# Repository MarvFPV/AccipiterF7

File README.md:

# Accipiter F7
A flight controller built for Rotorflight firmware and their F7A target. 
For more info go check out my [blog entry](https://mschnabel.com/2025/01/27/AccipiterF7/) on it!

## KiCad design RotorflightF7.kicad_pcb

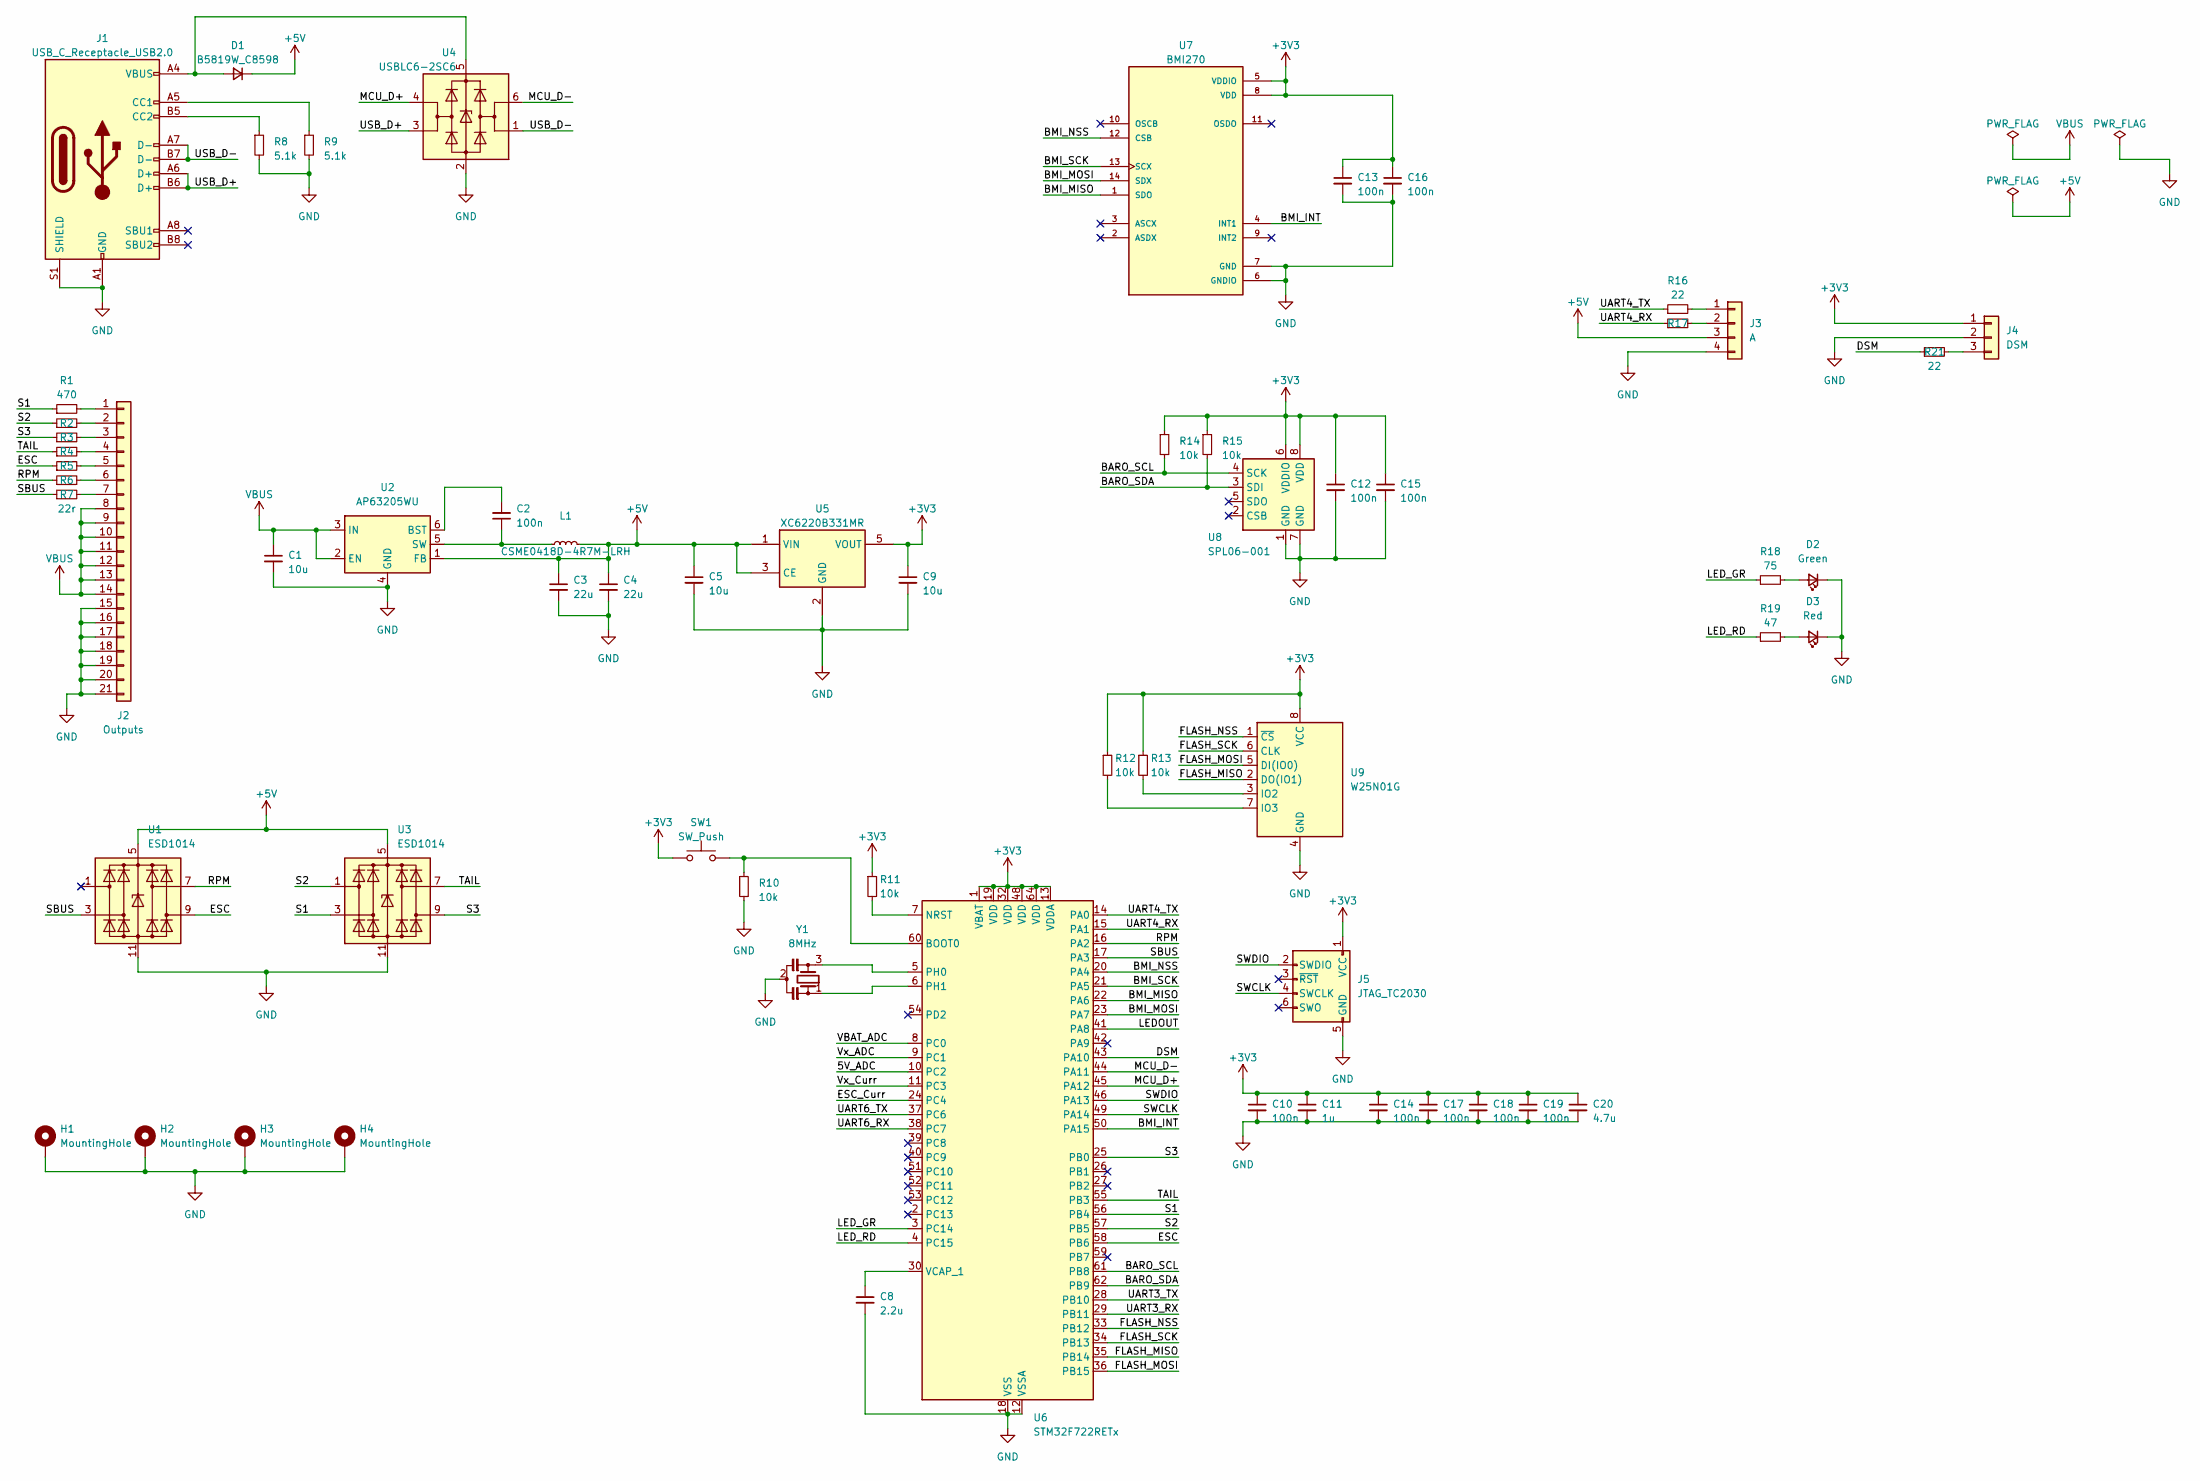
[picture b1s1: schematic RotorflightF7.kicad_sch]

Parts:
C1, C5, C9: 10u; C_0603_1608Metric
C2, C10, C12, C13, C14, C15, C16, C17, C18, C19: 100n; C_0402_1005Metric
C3, C4: 22u; C_0603_1608Metric
C8: 2.2u; C_0402_1005Metric
C11: 1u; C_0402_1005Metric
C20: 4.7u; C_0402_1005Metric
D1: B5819W_C8598; D_SOD-123
D2: Green; LED_0603_1608Metric
D3: Red; LED_0603_1608Metric
H1, H2, H3, H4: MountingHole; MountingHole_2.2mm_M2_Pad_Via
J1: USB_C_Receptacle_USB2.0; USB_C_Receptacle_HRO_TYPE-C-31-M-12
J2: Outputs; 7xServo_Vertical
J3: A; JST_GH_BM04B-GHS-TBT_1x04-1MP_P1.25mm_Vertical
J4: DSM; JST_ZH_B3B-ZR_1x03_P1.50mm_Vertical
J5: JTAG_TC2030; CON_TC2030_outlined
L1: CSME0418D-4R7M-LRH; L_Vishay_IFSC-1515AH_4x4x1.8mm
R1, R2, R3, R4, R5, R6: 470; R_0402_1005Metric
R7: 22r; R_0402_1005Metric
R8, R9: 5.1k; R_0402_1005Metric
R10, R11, R12, R13, R14, R15: 10k; R_0402_1005Metric
R16, R17, R21: 22; R_0402_1005Metric
R18: 75; R_0402_1005Metric
R19: 47; R_0402_1005Metric
SW1: SW_Push; SW_Push_SPST_NO_Alps_SKRK
U1, U3: ESD1014; DFN-10-1EP_2.6x2.6mm_P0.5mm_EP1.3x2.2mm
U2: AP63205WU; TSOT-23-6
U4: USBLC6-2SC6; SOT-23-6
U5: XC6220B331MR; SOT-23-5
U6: STM32F722RETx; LQFP-64_10x10mm_P0.5mm
U7: BMI270; XDCR_BMI270
U8: SPL06-001; Bosch_LGA-8_2x2.5mm_P0.65mm_ClockwisePinNumbering
U9: W25N01G; WSON-8-1EP_8x6mm_P1.27mm_EP3.4x4.3mm
Y1: 8MHz; Resonator_SMD_Murata_CSTxExxV-3Pin_3.0x1.1mm

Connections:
+3V3: C9.1, C10.1, C11.1, C12.1, C13.1, C14.1, C15.1, C16.1, C17.1, C18.1, C19.1, C20.1, J4.1, J5.1 (VCC), R11.1, R12.1, R13.1, R14.1, R15.1, SW1.1, U5.5 (VOUT), U6.1 (VBAT), U6.13 (VDDA), U6.19 (VDD), U6.32 (VDD), U6.48 (VDD), U6.64 (VDD), U7.5 (VDDIO), U7.8 (VDD), U8.6 (VDDIO), U8.8 (VDD), U9.8 (VCC)
+5V: C3.1, C4.1, C5.1, D1.1 (K), J3.3, L1.2, U1.5 (VBUS), U2.1 (FB), U3.5 (VBUS), U5.1 (VIN), U5.3 (CE)
/5V_ADC: U6.10 (PC2)
/BARO_SCL: R14.2, U6.61 (PB8), U8.4 (SCK)
/BARO_SDA: R15.2, U6.62 (PB9), U8.3 (SDI)
/BMI_INT: U6.50 (PA15), U7.4 (INT1)
/BMI_MISO: U6.22 (PA6), U7.1 (SDO)
/BMI_MOSI: U6.23 (PA7), U7.14 (SDX)
/BMI_NSS: U6.20 (PA4), U7.12 (CSB)
/BMI_SCK: U6.21 (PA5), U7.13 (SCX)
/DSM: R21.1, U6.43 (PA10)
/ESC: R5.1, U1.9 (I/O4), U6.58 (PB6)
/ESC_Curr: U6.24 (PC4)
/FLASH_MISO: U6.35 (PB14), U9.2 (DO(IO1))
/FLASH_MOSI: U6.36 (PB15), U9.5 (DI(IO0))
/FLASH_NSS: U6.33 (PB12), U9.1 (~CS)
/FLASH_SCK: U6.34 (PB13), U9.6 (CLK)
/LEDOUT: U6.41 (PA8)
/LED_GR: R18.1, U6.3 (PC14)
/LED_RD: R19.1, U6.4 (PC15)
/MCU_D+: U4.4 (I/O2), U6.45 (PA12)
/MCU_D-: U4.6 (I/O1), U6.44 (PA11)
/RPM: R6.1, U1.7 (I/O3), U6.16 (PA2)
/S1: R1.1, U3.3 (I/O2), U6.56 (PB4)
/S2: R2.1, U3.1 (I/O1), U6.57 (PB5)
/S3: R3.1, U3.9 (I/O4), U6.25 (PB0)
/SBUS: R7.1, U1.3 (I/O2), U6.17 (PA3)
/SWCLK: J5.4 (SWCLK), U6.49 (PA14)
/SWDIO: J5.2 (SWDIO), U6.46 (PA13)
/TAIL: R4.1, U3.7 (I/O3), U6.55 (PB3)
/UART3_RX: U6.29 (PB11)
/UART3_TX: U6.28 (PB10)
/UART4_RX: R17.1, U6.15 (PA1)
/UART4_TX: R16.1, U6.14 (PA0)
/UART6_RX: U6.38 (PC7)
/UART6_TX: U6.37 (PC6)
/USB_D+: J1.A6 (D+), J1.B6 (D+), U4.3 (I/O2)
/USB_D-: J1.A7 (D-), J1.B7 (D-), U4.1 (I/O1)
/VBAT_ADC: U6.8 (PC0)
/Vx_ADC: U6.9 (PC1)
/Vx_Curr: U6.11 (PC3)
GND: C1.2, C3.2, C4.2, C5.2, C8.2, C9.2, C10.2, C11.2, C12.2, C13.2, C14.2, C15.2, C16.2, C17.2, C18.2, C19.2, C20.2, D2.1 (K), D3.1 (K), H1.1, H2.1, H3.1, H4.1, J1.A1 (GND), J1.A12 (GND), J1.B1 (GND), J1.B12 (GND), J1.S1 (SHIELD), J2.15, J2.16, J2.17, J2.18, J2.19, J2.20, J2.21, J3.4, J4.2, J5.5 (GND), R8.2, R9.2, R10.2, U1.11 (GND), U2.4 (GND), U3.11 (GND), U4.2 (GND), U5.2 (GND), U6.12 (VSSA), U6.18 (VSS), U6.31 (VSS), U6.47 (VSS), U6.63 (VSS), U7.6 (GNDIO), U7.7 (GND), U8.1 (GND), U8.7 (GND), U9.4 (GND), Y1.2
unnamed: D1.2 (A), J1.A4 (VBUS), J1.A9 (VBUS), J1.B4 (VBUS), J1.B9 (VBUS), U4.5 (VBUS)
unnamed: D2.2 (A), R18.2
unnamed: D3.2 (A), R19.2
unnamed: J1.A5 (CC1), R9.1
unnamed: J1.B5 (CC2), R8.1
unnamed: J2.1, R1.2
unnamed: J2.2, R2.2
unnamed: J2.3, R3.2
unnamed: J2.4, R4.2
unnamed: J2.5, R5.2
unnamed: J2.6, R6.2
unnamed: J2.7, R7.2
unnamed: J3.1, R16.2
unnamed: J3.2, R17.2
unnamed: J4.3, R21.2
unnamed: C2.2, U2.6 (BST)
unnamed: C2.1, L1.1, U2.5 (SW)
unnamed: R10.1, SW1.2, U6.60 (BOOT0)
unnamed: R11.2, U6.7 (NRST)
unnamed: U6.5 (PH0), Y1.3
unnamed: U6.6 (PH1), Y1.1
unnamed: C8.1, U6.30 (VCAP_1)
unnamed: R13.2, U9.3 (IO2)
unnamed: R12.2, U9.7 (IO3)
VBUS: C1.1, J2.8, J2.9, J2.10, J2.11, J2.12, J2.13, J2.14, U2.2 (EN), U2.3 (IN)

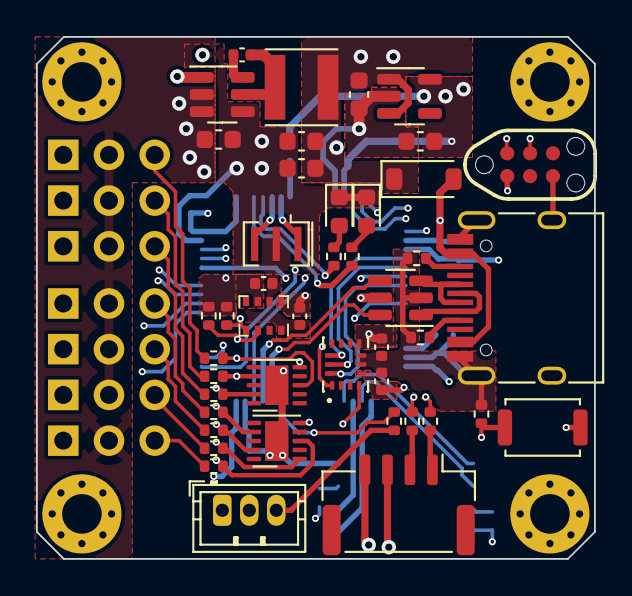
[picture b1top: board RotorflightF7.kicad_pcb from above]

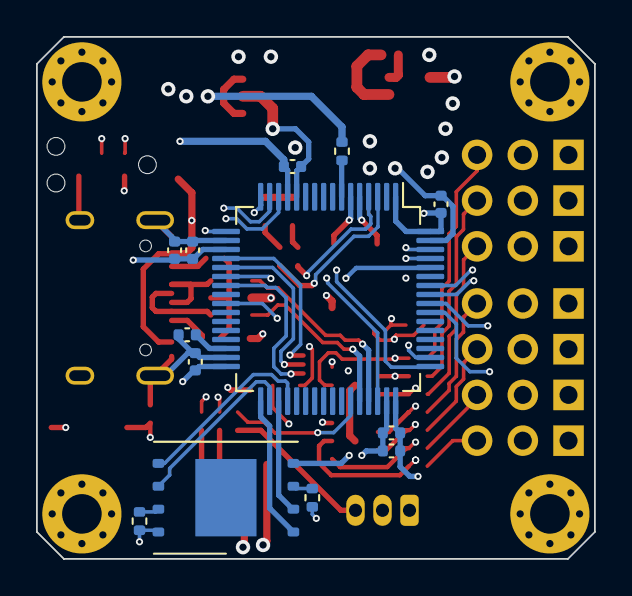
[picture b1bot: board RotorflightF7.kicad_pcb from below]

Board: 6 copper layers, 31.0 x 29.0 mm, 62 parts (13 on the bottom side), 57 nets.

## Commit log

2023-10-11 stuff
2025-01-27 schematic visual updates
2025-01-27 who decided to commit a lock file? (me)
2025-01-27 adding cad, renaming, cleaning up
2025-01-27 more cleanup
2025-01-27 Create LICENSE
